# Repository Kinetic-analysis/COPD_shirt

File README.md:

# COPD_shirt
COPD-shirt repository for software, firmware and hardware

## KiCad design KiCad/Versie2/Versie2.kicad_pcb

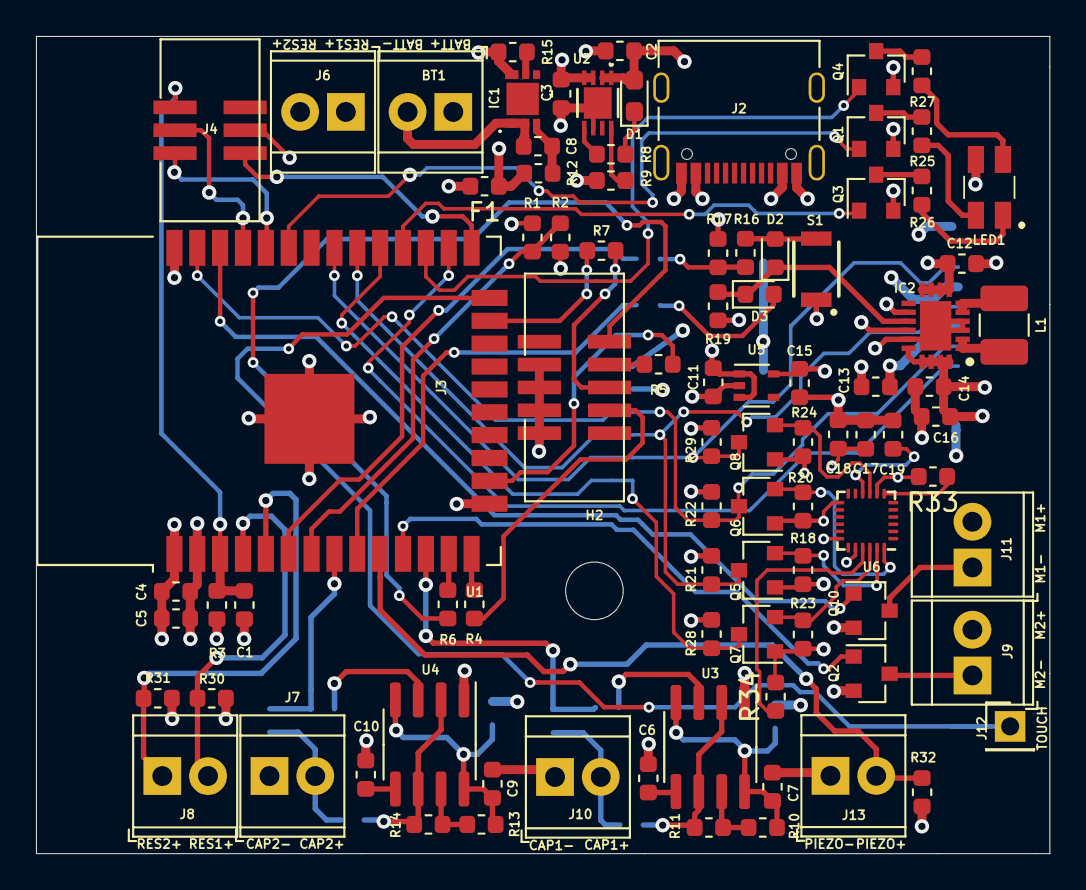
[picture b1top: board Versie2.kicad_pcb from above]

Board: 4 copper layers, 56.3 x 45.4 mm, 102 parts (0 on the bottom side), 76 nets.

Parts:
BT1: INR; TerminalBlock_TE_282834-2_1x02_P2.54mm_Horizontal
C1, C11, C15, C17: 1uF; C_0603_1608Metric
C2, C3: 4.7uF; C_0603_1608Metric
C4, C7, C8, C9, C16, C18, C19: 100nF; C_0603_1608Metric
C5: 10uF; C_0603_1608Metric
C6, C10: 10nF; C_0603_1608Metric
C12, C13, C14: 22uF; C_0603_1608Metric
D1: LED; LED_0603_1608Metric_Pad1.05x0.95mm_HandSolder
D2, D3: SD1206S040S0R5; D_0603_1608Metric
F1: Polyfuse_Small; Fuse_0603_1608Metric
H2: MountingHole; MountingHole_3.2mm_M3
IC1: AP9221SA-CC-HAC-7; AP9211SAANHAC7
IC2: ISL91107IRTNZ-T7A
J1: Micro_SD_Card_Det; microSD_HC_Molex_104031-0811
J2: USB_C_Receptacle_USB3.0; USB_C_Receptacle_Palconn_UTC16-G
J3: JTAG; Pin_Header_2x5_1.27mm_CONN
J4: Programmer; Pin_Header_2x3_1.27mm_CONN
J5: Conn_01x06_Male; IMU_Testpins
J6, J7, J8, J9, J10, J11, J13: Screw_Terminal_01x02; TerminalBlock_TE_282834-2_1x02_P2.54mm_Horizontal
J12: Conn_01x01_Male; PinHeader_1x01_P2.54mm_Vertical
JP1, JP2, JP3, JP4, JP5, JP6, JP7, JP8, JP9, JP10: SolderJumper_2_Open; SolderJumper-2_P1.3mm_Open_Pad1.0x1.5mm
L1: 1uH; L_1210_3225Metric_Pad1.42x2.65mm_HandSolder
LED1: SMTL4-RGY; SMTL4RGY
Q1, Q2, Q3, Q4, Q5, Q6, Q7, Q8, Q10: Q_NMOS_GSD; SOT-23
R1, R2, R16, R17, R19: 100k; R_0603_1608Metric
R3, R10, R13, R32: 10k; R_0603_1608Metric
R4, R5, R6, R7: 100; R_0603_1608Metric
R8: 470; R_0603_1608Metric
R9: 2k; R_0603_1608Metric
R11, R14: 180k; R_0603_1608Metric
R12: 330; R_0603_1608Metric
R15: 2.7k; R_0603_1608Metric
R18, R20, R21, R22, R23, R24, R28, R29, R33, R34: 2.2k; R_0603_1608Metric
R25, R26, R27: 120; R_0603_1608Metric
R30, R31: 1k; R_0603_1608Metric
S1: B3U-1000P
U1: ESP32-WROOM-32
U2: MCP73831T-2ATI_MC; MCP73831T-2ATI&slash_MC
U3, U4: NE555DR; SOIC-8_3.9x4.9mm_P1.27mm
U5: MIC5366-1.8YC5-TR; SOT-353_SC-70-5
U6: ICM-20948; InvenSense_QFN-24_3x3mm_P0.4mm

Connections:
+1V8: C15.1, C17.1, C18.1, Q5.1, Q6.1, Q7.1, Q8.1, R18.1, R20.1, R23.1, R24.1, R33.2, R34.2, U5.5, U6.8, U6.13
+3V3: C4.1, C5.1, C11.2, C13.2, C14.2, C16.1, IC2.16, IC2.17, IC2.18, IC2.19, IC2.20, J1.4, J5.5, J6.1, J6.2, J9.2, J11.2, JP1.1, JP4.1, R3.1, R21.1, R22.1, R28.1, R29.1, U1.2, U5.1, U5.3
+5V: C2.1, D1.2, J2.A4, J2.A9, J2.B4, J2.B9, U2.1, U2.2
+BATT: C12.2, F1.2, IC2.7, IC2.8, IC2.9, IC2.10, IC2.12, IC2.14, LED1.4, R1.1, S1.1
Batt_Before_Fuse: BT1.1, C3.1, F1.1, R12.2, U2.3, U2.4
Battery_VOLTAGE: R1.2, R2.1, U1.7
Capacitive_Stretch1: J10.2, JP3.2, JP7.1
Capacitive_Stretch1_OUT: JP2.2, JP7.2, U1.12
Capacitive_Stretch2: J7.2, JP6.2, JP10.1
Capacitive_Stretch2_OUT: JP5.2, JP10.2, U1.8
DC-DC_ENABLE: D2.1, D3.1, IC2.13, R19.1
ESP_EN: C1.2, J4.1, R3.2, U1.3
ESP_IMU_CS: J5.1, Q7.3, R28.2, U1.29
ESP_IO0: J4.4, U1.25
ESP_MTCK: J3.9, R5.2
ESP_MTDI: J3.7, R4.2
ESP_MTDO: J3.8, R7.2
ESP_MTMS: J3.10, R6.2
ESP_RXD: J4.3, U1.34
ESP_SD_CS: J1.2, U1.26
ESP_SPI_CLK: J1.5, J5.3, Q5.3, R21.2, U1.30
ESP_SPI_MISO: J1.7, J5.2, Q8.3, R29.2, U1.31
ESP_SPI_MOSI: J1.3, J5.4, Q6.3, R22.2, U1.37
ESP_TXD: J4.2, U1.35
GND: C1.1, C2.2, C3.2, C4.2, C5.2, C6.2, C7.2, C9.2, C10.2, C11.1, C12.1, C13.1, C14.1, C15.2, C16.2, C17.2, C18.2, C19.2, IC1.6, IC2.3, IC2.4, IC2.15, IC2.21, J1.6, J1.11, J2.A1, J2.A12, J2.B1, J2.B12, J2.S1, J3.2, J3.3, J3.4, J3.5, J4.5, J5.6, J7.1, J10.1, J13.1, Q1.2, Q2.2, Q3.2, Q4.2, Q10.2, R2.2, R9.2, R15.2, R17.2, R19.2, R30.2, R31.1, R32.1, U1.1, U1.15, U1.38, U1.39, U2.6, U2.9, U3.1, U4.1, U5.2, U6.18, U6.20
Green_LED: Q3.1, U1.28
IMU_CLK: Q5.2, R18.2, U6.23
IMU_CS: Q7.2, R23.2, U6.22
IMU_MISO: Q8.2, R24.2, U6.9
IMU_MOSI: Q6.2, R20.2, U6.24
LATCH: D3.2, JP8.2
unnamed: BT1.2, C8.1, IC1.1, IC1.2
unnamed: C6.1, U3.5
unnamed: C7.1, JP1.2, R10.1, U3.4, U3.8
unnamed: C8.2, IC1.3, R12.1
unnamed: C9.1, JP4.2, R13.1, U4.4, U4.8
unnamed: C10.1, U4.5
unnamed: C19.1, U6.10
unnamed: D1.1, R8.1
unnamed: D2.2, R16.1, S1.2
unnamed: IC1.5, R15.1
unnamed: IC2.1, IC2.2, L1.2
unnamed: IC2.5, IC2.6, L1.1
unnamed: J9.1, Q2.3
unnamed: J11.1, Q10.3
unnamed: JP2.1, U3.3
unnamed: JP3.1, R11.2, U3.2, U3.6
unnamed: JP5.1, U4.3
unnamed: JP6.1, R14.2, U4.2, U4.6
unnamed: LED1.1, R26.1
unnamed: LED1.2, R27.1
unnamed: LED1.3, R25.1
unnamed: Q1.3, R25.2
unnamed: Q3.3, R26.2
unnamed: Q4.3, R27.2
unnamed: R4.1, U1.14
unnamed: R5.1, U1.16
unnamed: R6.1, U1.13
unnamed: R7.1, U1.23
unnamed: R8.2, U2.5
unnamed: R9.1, U2.8
unnamed: R10.2, R11.1, U3.7
unnamed: R13.2, R14.1, U4.7
unnamed: R33.1, U6.7
unnamed: R34.1, U6.21
Piezo_Speaker: J13.2, R32.2, U1.10
Red_LED: Q1.1, U1.33
Resistive_Stretch1: J8.2, R30.1, U1.4
Resistive_Stretch2: J8.1, R31.2, U1.5
SENSE: JP9.2, R16.2, R17.1
Touch_Pad: J12.1, U1.24
Vibrator_MOTOR1: Q10.1, U1.36
Vibrator_MOTOR2: Q2.1, U1.11
Yellow_LED: Q4.1, U1.27
uC_LATCH: JP8.1, U1.9
uC_SENSE: JP9.1, U1.6

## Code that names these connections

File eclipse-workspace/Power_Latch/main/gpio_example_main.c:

#include <stdio.h>
#include "freertos/FreeRTOS.h"
#include "freertos/task.h"
#include "driver/gpio.h"
#include "sdkconfig.h"
#include "driver/timer.h"

volatile uint64_t StartValue;
volatile uint64_t PeriodCount;
volatile int Aan_Uit = 0;

#define uC_SENSE			GPIO_NUM_16
#define uC_LATCH			GPIO_NUM_17
#define GREEN_LED			GPIO_NUM_25
#define YELLOW_LED			GPIO_NUM_26
#define RED_LED				GPIO_NUM_27
#define VIBRATOR_MOTOR		GPIO_NUM_33
#define RESISTIVE_STRETCH	GPIO_NUM_34
#define BATT_VOLT			GPIO_NUM_35

void IRAM_ATTR Power_Latch_ISR_Handler(void *arg)
{
		gpio_set_level(uC_LATCH, 0);
}

static void GPIO_init(void)
{
	gpio_pad_select_gpio(uC_SENSE);
	gpio_pad_select_gpio(uC_LATCH);
	gpio_pad_select_gpio(GREEN_LED);
	gpio_pad_select_gpio(YELLOW_LED);
	gpio_pad_select_gpio(RED_LED);
	gpio_pad_select_gpio(VIBRATOR_MOTOR);
	gpio_pad_select_gpio(RESISTIVE_STRETCH);
	gpio_pad_select_gpio(BATT_VOLT);

	gpio_set_direction(uC_SENSE, GPIO_MODE_INPUT);
	gpio_set_direction(uC_LATCH, GPIO_MODE_OUTPUT);
	gpio_set_direction(GREEN_LED, GPIO_MODE_OUTPUT);
	gpio_set_direction(YELLOW_LED, GPIO_MODE_OUTPUT);
	gpio_set_direction(RED_LED, GPIO_MODE_OUTPUT);
	gpio_set_direction(VIBRATOR_MOTOR, GPIO_MODE_OUTPUT);
	gpio_set_direction(RESISTIVE_STRETCH, GPIO_MODE_INPUT);
	gpio_set_direction(BATT_VOLT, GPIO_MODE_INPUT);

	gpio_set_level(GREEN_LED, 0);
	gpio_set_level(YELLOW_LED, 0);
	gpio_set_level(RED_LED, 0);
	gpio_set_level(VIBRATOR_MOTOR, 0);
	gpio_set_level(uC_LATCH, 1);

//	gpio_set_intr_type(uC_SENSE, GPIO_INTR_POSEDGE);
//	gpio_install_isr_service(0);
//	gpio_isr_handler_add(uC_SENSE, Power_Latch_ISR_Handler, NULL);
}

void app_main(void)
{
	GPIO_init();
	printf("ESP STARTED\n");
	vTaskDelay(2500 / portTICK_PERIOD_MS);
	gpio_set_intr_type(uC_SENSE, GPIO_INTR_POSEDGE);
	gpio_install_isr_service(0);
	gpio_isr_handler_add(uC_SENSE, Power_Latch_ISR_Handler, NULL);

    while(1) {
    	printf("Hello World\n");
    	vTaskDelay(250 / portTICK_PERIOD_MS);
    }
}

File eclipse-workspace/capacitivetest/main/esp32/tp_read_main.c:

/* Touch Pad Read Example

   This example code is in the Public Domain (or CC0 licensed, at your option.)

   Unless required by applicable law or agreed to in writing, this
   software is distributed on an "AS IS" BASIS, WITHOUT WARRANTIES OR
   CONDITIONS OF ANY KIND, either express or implied.
*/
#include <stdio.h>
#include "freertos/FreeRTOS.h"
#include "freertos/task.h"
#include "driver/touch_pad.h"
#include "esp_log.h"
#include "driver/gpio.h"
#include "driver/timer.h"
#include <inttypes.h>

#define TOUCH_PAD_NO_CHANGE   (-1)
#define TOUCH_THRESH_NO_USE   (0)
#define TOUCH_FILTER_MODE_EN  (1)
#define TOUCHPAD_FILTER_TOUCH_PERIOD (1)
volatile int64_t starttime;
volatile int knop = 0;

#define Power_sense_pin			GPIO_NUM_34
#define Power_on_off_pin		GPIO_NUM_33
#define Green_led_pin			GPIO_NUM_17
#define Yellow_led_pin			GPIO_NUM_16
#define Red_led_pin				GPIO_NUM_21
#define Vibrator_motor1_pin		GPIO_NUM_22
#define Vibrator_motor2_pin		GPIO_NUM_26
#define Touch_sensor			GPIO_NUM_2
#define Battery					GPIO_NUM_35

volatile uint64_t StartValue = 0;
volatile uint64_t PeriodCount = 0;
//volatile uint64_t counter;

void IRAM_ATTR Touchpad_ISR_Handler(void *arg)
{
	gpio_set_level(Power_on_off_pin, 0);
}

void IRAM_ATTR CapStretch_ISR_Handler(void *arg)
{
	uint64_t counter = 0;
	timer_get_counter_value(TIMER_GROUP_1, TIMER_1, &counter);
	uint64_t TempVal = counter;
	PeriodCount = TempVal - StartValue;
	StartValue = TempVal;
	//printf("KUTZOOI\n");
}

static void Cap_NE555_Task(void *pvParameter)
{
	int64_t Value = 0;
	int64_t temp = 0;
	int64_t microseconden = 0;
	while(1)
	{
		temp = esp_timer_get_time();
		microseconden = temp - starttime;
		Value = PeriodCount;
		printf("%" PRId64 "," "%" PRId64 "\n", microseconden, Value);
		//printf("%" PRId64 "\n", Value);
		//printf("Hallo!\n");
		vTaskDelay(100 / portTICK_PERIOD_MS);
	}
}

static void GPIO_init(void)
{
	gpio_pad_select_gpio(Power_sense_pin);
	gpio_pad_select_gpio(Power_on_off_pin);
	gpio_pad_select_gpio(Green_led_pin);
	gpio_pad_select_gpio(Yellow_led_pin);
	gpio_pad_select_gpio(Red_led_pin);
	gpio_pad_select_gpio(Battery);

	gpio_set_direction(Power_sense_pin, GPIO_MODE_INPUT);
	gpio_set_direction(Power_on_off_pin, GPIO_MODE_OUTPUT);
	gpio_set_direction(Green_led_pin, GPIO_MODE_OUTPUT);
	gpio_set_direction(Yellow_led_pin, GPIO_MODE_OUTPUT);
	gpio_set_direction(Red_led_pin, GPIO_MODE_OUTPUT);
	gpio_set_direction(Battery, GPIO_MODE_INPUT);

	gpio_set_level(Green_led_pin, 1);
	gpio_set_level(Yellow_led_pin, 0);
	gpio_set_level(Red_led_pin, 0);
	gpio_set_level(Power_on_off_pin, 1); //Zet systeem meteen aan
}
/*
  Read values sensed at all available touch pads.
 Print out values in a loop on a serial monitor.
 */
static void tp_example_read_task(void *pvParameter)
{
	uint16_t counter = 0;
    uint16_t touch_value;
    uint16_t touch_filter_value;
    while (1) {
    	int64_t temp = 0;
    	int64_t microseconden = 0;
    	temp = esp_timer_get_time();
    	microseconden = temp - starttime;

    	touch_pad_read(TOUCH_PAD_NUM7, &touch_filter_value);

        printf("%" PRId64 ", %4d\n", microseconden, touch_filter_value);
    	//printf("%4d\n", touch_filter_value);
        vTaskDelay(10 / portTICK_PERIOD_MS);
    }
}

static void tp_example_touch_pad_init(void)
{
    touch_pad_config(TOUCH_PAD_NUM7, TOUCH_THRESH_NO_USE);
}

void app_main(void)
{
	GPIO_init();
    touch_pad_init();

    touch_pad_set_voltage(TOUCH_HVOLT_2V4, TOUCH_LVOLT_0V5, TOUCH_HVOLT_ATTEN_1V5);
    touch_pad_set_cnt_mode(TOUCH_PAD_NUM7, TOUCH_PAD_SLOPE_1, TOUCH_PAD_TIE_OPT_LOW);
    touch_pad_set_meas_time(0x0001, 0xffff);

    tp_example_touch_pad_init();

	timer_config_t capSensor;
    capSensor.alarm_en = TIMER_ALARM_DIS;
    capSensor.counter_en = TIMER_START;
    capSensor.intr_type = TIMER_INTR_LEVEL;
    capSensor.counter_dir = TIMER_COUNT_UP;
    capSensor.auto_reload = TIMER_AUTORELOAD_DIS;
    capSensor.divider = 2;

    vTaskDelay(5000 / portTICK_PERIOD_MS);
    timer_init(TIMER_GROUP_1, TIMER_1, &capSensor);
	gpio_pad_select_gpio(GPIO_NUM_32);
	//gpio_pad_select_gpio(Power_sense_pin);
	gpio_set_direction(GPIO_NUM_32, GPIO_MODE_INPUT);
	//gpio_set_direction(Power_sense_pin, GPIO_MODE_INPUT);
	gpio_set_intr_type(GPIO_NUM_32, GPIO_INTR_NEGEDGE);
	//gpio_set_intr_type(Power_sense_pin, GPIO_INTR_NEGEDGE);
	gpio_install_isr_service(0);
	gpio_isr_handler_add(GPIO_NUM_32, CapStretch_ISR_Handler, NULL);
	//gpio_isr_handler_add(Power_sense_pin, Touchpad_ISR_Handler, NULL);




    // Start task to read values sensed by pads
    //xTaskCreate(&tp_example_read_task, "touch_pad_read_task", 2048, NULL, 5, NULL);
	xTaskCreate(&Cap_NE555_Task, "Capacitive Stretch Sensor NE555", 2048, NULL, 5, NULL);
    starttime = esp_timer_get_time();
    //xTaskCreate(&tp_example_led_task, "touch_pad_led_task", 2048, NULL, 4, NULL);
}

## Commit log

2021-02-26 KiCad project aangemaakt
2021-02-26 Charger+Microcontroller+DC/DC schakeling
2021-03-01 KiCad schakeling aangepast + LTSpice Power Latch simulatie
2021-03-11 PCB Versie 1
2021-03-12 H2, C13, C14 aangepast
2021-03-12 5x6cm PCB en silkscreen update
2021-03-15 BOM Lijst
2021-03-29 IMU Footprint + Solder Jumper Power Latch
2021-03-30 Arduino code voor CapStretch en LTSpice relaxation oscillator simulatie
2021-04-02 Eclipse workspace
2021-04-02 Eclipse workspace update
2021-04-05 Wi-Fi UDP + python
2021-04-05 Simpel data visualisatie
2021-04-05 Data opslag in txt bestand
2021-04-05 Cap Stretch workspace fix
2021-04-05 Revert "Cap Stretch workspace fix"
    This reverts commit ae097c9e7e08dc22c9a6af32dc6dd1f8fa1f5098.
2021-04-05 revert commit
2021-04-05 TCP ESP32 + Python
2021-04-05 LTSpice NE555
2021-04-05 LTSpice NE555 10nF added
2021-04-06 idf.py menuconfig
2021-04-08 Cap stretch + LTSpice NE555 adjustment
2021-04-08 Arduino Frequency Meter
2021-04-08 Interrupt+Timer Eclipse (CapSensor)
2021-04-08 NE555 Update LTSpice
2021-04-10 PWM_Motor example
2021-04-11 KiCad Library fix
2021-04-12 Main Code update
2021-04-12 Integratie Battery+LED+ResistiveStretch
2021-04-12 Power Latch
2021-04-12 Integratie Alles
2021-04-13 KiCad begin versie2
2021-04-13 KiCad Cap Stretch schakeling
2021-04-14 KiCad IMU
2021-04-14 KiCad Buzzer + SD Card
2021-04-15 KiCad Schakeling update
2021-04-15 KiCad PCB IC Layout
2021-04-16 KiCad Footprints adjusted
2021-04-16 KiCad Plaatsing componenten
2021-04-16 KiCad New layout
2021-04-17 KiCad PCB Versie 2 af
2021-04-18 BOMLIST
2021-04-18 BOM en bestel files aangepast
2021-04-24 Main code met tijdstip
2021-04-25 IMU Sensor write + read register
2021-04-26 NE555 LTSpice equivalent sensor
2021-04-27 IMU Sensor accelero + gyro
2021-04-29 IMU Accelero+Gyro werkend
2021-04-29 Magneto werkend
2021-04-29 IMU accelero+gyro+magneto samen werkend
2021-05-03 Firmware opgeschoond
2021-05-04 Programmeer Guide V1
2021-05-05 CapacitiveTouch Tests aanpassingen
2021-05-07 PCB Versie 2 integratie, sensor, imu, battery management, motor, tcp client
2021-05-09 Piezo done en sdcard example
2021-05-10 SD_Card arduino ESP32
2021-06-02 Deelsystemen ingedeeld met C en H files
2021-06-08 Github error fix
2021-06-08 SD met IMU initialisatie
2021-06-09 Wi-Fi data versturen en data visualisatie update
2021-06-18 NE555 + Wi-Fi werkend
2021-07-06 Capacitive_only
2021-07-06 hotspot test

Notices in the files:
parts and their libraries:
Copyright 2016 Accelerated Designs. All rights reserved.
